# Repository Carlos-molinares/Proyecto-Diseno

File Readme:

Proyecto Diseño 
Carlos Andrés Molinares Rojas - 2210435
Jose Luis Parra Villamizar - 2210399

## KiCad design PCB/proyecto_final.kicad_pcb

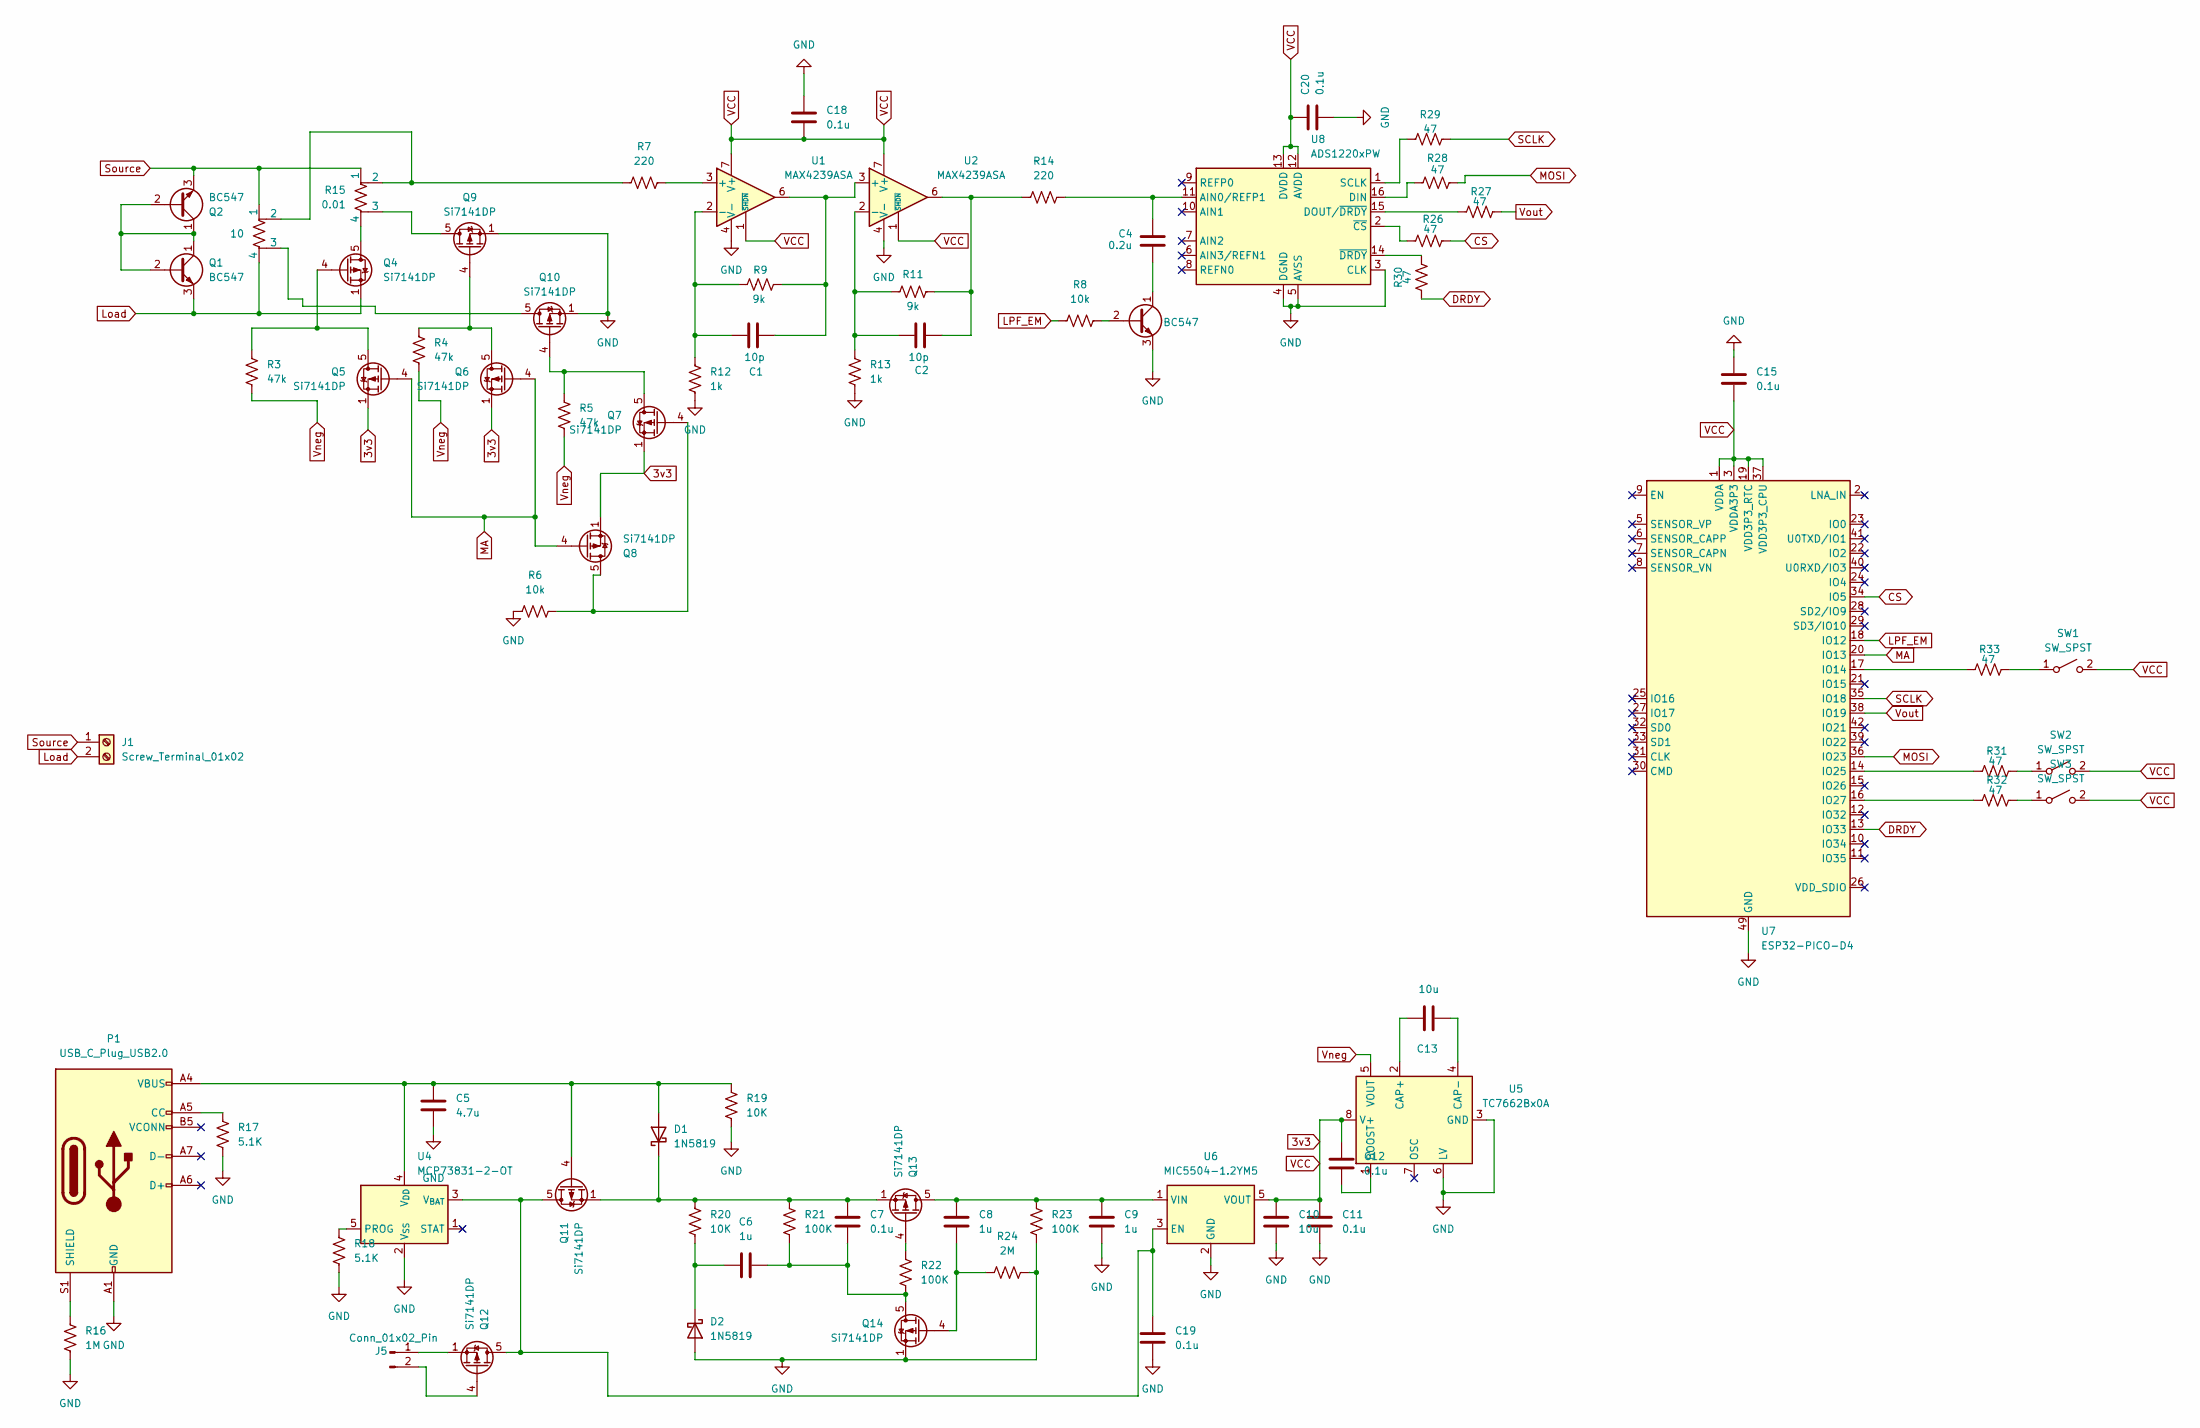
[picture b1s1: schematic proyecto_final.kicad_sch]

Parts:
C1, C2: 10p; C_0201_0603Metric
C4: 0.2u; C_0201_0603Metric
C5: 4.7u; C_0201_0603Metric
C6, C8, C9: 1u; C_0201_0603Metric
C7, C11, C12, C15, C18, C19, C20: 0.1u; C_0201_0603Metric
C10, C13: 10u; C_0201_0603Metric
D1, D2: 1N5819; D_DO-41_SOD81_P10.16mm_Horizontal
J1: Screw_Terminal_01x02; TerminalBlock_Altech_AK300-2_P5.00mm
J5: Conn_01x02_Pin; JST_EH_B2B-EH-A_1x02_P2.50mm_Vertical
P1: USB_C_Plug_USB2.0; USB_C_Plug_ShenzhenJingTuoJin_918-118A2021Y40002_Vertical
Q1, Q2, Q3: BC547; TO-92_Inline
Q4, Q5, Q6, Q7, Q8, Q9, Q10, Q11, Q12, Q13, Q14: Si7141DP; PowerPAK_SO-8_Single
R3, R4, R5: 47k; R_0201_0603Metric
R6, R8: 10k; R_0201_0603Metric
R7, R14: 220; R_0201_0603Metric
R9, R11: 9k; R_0201_0603Metric
R10: 10; R_Shunt_Ohmite_LVK12
R12, R13: 1k; R_0201_0603Metric
R15: 0.01; R_Shunt_Ohmite_LVK12
R16: 1M; R_0201_0603Metric
R17, R18: 5.1K; R_0201_0603Metric
R19, R20: 10K; R_0201_0603Metric
R21, R22, R23: 100K; R_0201_0603Metric
R24: 2M; R_0201_0603Metric
R26, R27, R28, R29, R30, R31, R32, R33: 47; R_0201_0603Metric
SW1, SW2, SW3: SW_SPST; SW_DIP_SPSTx01_Slide_6.7x4.1mm_W7.62mm_P2.54mm_LowProfile
U1, U2: MAX4239ASA; SOIC-8_3.9x4.9mm_P1.27mm
U4: MCP73831-2-OT; SOT-23-5
U5: TC7662Bx0A; SOIC-8_3.9x4.9mm_P1.27mm
U6: MIC5504-1.2YM5; SOT-23-5
U7: ESP32-PICO-D4; QFN-48-1EP_7x7mm_P0.5mm_EP5.3x5.3mm
U8: ADS1220xPW; TSSOP-16_4.4x5mm_P0.65mm

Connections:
3v3: C10.1, C11.1, C12.1, C15.2, C18.2, C20.2, Q5.1 (S), Q5.2 (S), Q5.3 (S), Q6.1 (S), Q6.2 (S), Q6.3 (S), Q7.1 (S), Q7.2 (S), Q7.3 (S), Q8.1 (S), Q8.2 (S), Q8.3 (S), SW1.2 (B), SW2.2 (B), SW3.2 (B), U1.1 (~SHDN), U1.7 (V+), U2.1 (~SHDN), U2.7 (V+), U5.8 (V+), U6.5 (VOUT), U7.1 (VDDA), U7.3 (VDDA3P3), U7.4 (VDDA3P3), U7.19 (VDD3P3_RTC), U7.37 (VDD3P3_CPU), U7.43 (VDDA), U7.46 (VDDA), U8.12 (AVDD), U8.13 (DVDD)
CS: R26.1, U7.34 (IO5)
DRDY: R30.2, U7.13 (IO33)
GND: C5.1, C9.2, C10.2, C11.2, C15.1, C18.1, C19.2, C20.1, D2.2 (A), P1.A1 (GND), P1.A12 (GND), P1.B1 (GND), P1.B12 (GND), Q3.3 (E), Q9.1 (S), Q9.2 (S), Q9.3 (S), Q10.1 (S), Q10.2 (S), Q10.3 (S), Q14.1 (S), Q14.2 (S), Q14.3 (S), R6.2, R12.2, R13.2, R16.2, R17.2, R18.2, R19.2, R23.2, R24.2, U1.4 (V-), U2.4 (V-), U4.2 (V_{SS}), U5.3 (GND), U5.6 (LV), U6.2 (GND), U7.49 (GND), U8.3 (CLK), U8.4 (DGND), U8.5 (AVSS)
LPF_EM: R8.2, U7.18 (IO12)
Load: J1.2, Q1.3 (E), Q4.1 (S), Q4.2 (S), Q4.3 (S), R10.4
MA: Q5.4 (G), Q6.4 (G), Q8.4 (G), U7.20 (IO13)
MOSI: R28.1, U7.36 (IO23)
unnamed: C2.2, R11.1, R14.2, U2.6
unnamed: C5.2, D1.2 (A), P1.A4 (VBUS), P1.A9 (VBUS), P1.B4 (VBUS), P1.B9 (VBUS), Q11.4 (G), R19.1, U4.4 (V_{DD})
unnamed: C7.2, D1.1 (K), Q11.1 (S), Q11.2 (S), Q11.3 (S), Q13.1 (S), Q13.2 (S), Q13.3 (S), R20.1, R21.1
unnamed: C6.2, D2.1 (K), R20.2
unnamed: J5.1, Q12.1 (S), Q12.2 (S), Q12.3 (S)
unnamed: J5.2, Q12.4 (G)
unnamed: P1.A5 (CC), R17.1
unnamed: P1.S1 (SHIELD), R16.1
unnamed: Q1.1 (C), Q1.2 (B), Q2.1 (C), Q2.2 (B)
unnamed: Q3.2 (B), R8.1
unnamed: C4.1, Q3.1 (C)
unnamed: Q4.5 (D), R15.4
unnamed: Q4.4 (G), Q5.5 (D), R3.1
unnamed: Q6.5 (D), Q9.4 (G), R4.1
unnamed: Q7.4 (G), Q8.5 (D), R6.1
unnamed: Q9.5 (D), R15.3
unnamed: Q10.5 (D), R10.3
unnamed: Q7.5 (D), Q10.4 (G), R5.1
unnamed: C19.1, Q11.5 (D), Q12.5 (D), U4.3 (V_{BAT}), U6.3 (EN)
unnamed: C8.1, C9.1, Q13.5 (D), R23.1, U6.1 (VIN)
unnamed: Q13.4 (G), R22.1
unnamed: C6.1, C7.1, Q14.5 (D), R21.2, R22.2
unnamed: C8.2, Q14.4 (G), R24.1
unnamed: R7.2, R10.2, R15.2
unnamed: R33.1, SW1.1 (A)
unnamed: R31.1, SW2.1 (A)
unnamed: R32.1, SW3.1 (A)
unnamed: R7.1, U1.3 (+)
unnamed: C1.1, R9.2, R12.1, U1.2 (-)
unnamed: C1.2, R9.1, U1.6, U2.3 (+)
unnamed: C2.1, R11.2, R13.1, U2.2 (-)
unnamed: R18.1, U4.5 (PROG)
unnamed: C12.2, U5.1 (BOOST)
unnamed: C13.1, U5.2 (CAP+)
unnamed: C13.2, U5.4 (CAP-)
unnamed: R33.2, U7.17 (IO14)
unnamed: R31.2, U7.14 (IO25)
unnamed: R32.2, U7.16 (IO27)
unnamed: C4.2, R14.1, U8.11 (AIN0/REFP1)
unnamed: R28.2, U8.16 (DIN)
unnamed: R27.2, U8.15 (DOUT/~DRDY)
unnamed: R29.2, U8.1 (SCLK)
unnamed: R26.2, U8.2 (~CS)
unnamed: R30.1, U8.14 (~DRDY)
SCLK: R29.1, U7.35 (IO18)
Source: J1.1, Q2.3 (E), R10.1, R15.1
Vneg: R3.2, R4.2, R5.2, U5.5 (VOUT)
Vout: R27.1, U7.38 (IO19)

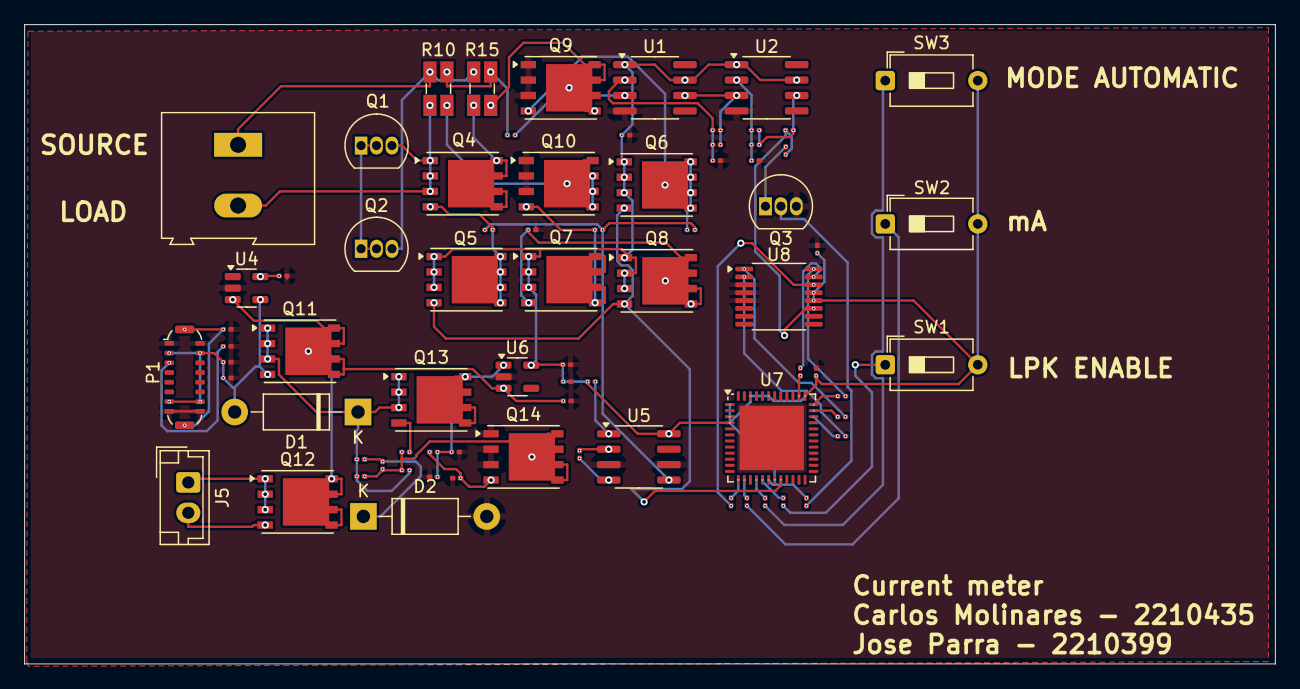
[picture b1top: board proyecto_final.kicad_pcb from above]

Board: 2 copper layers, 103.0 x 52.7 mm, 75 parts (0 on the bottom side), 56 nets.

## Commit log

2025-04-25 Create Readme
    Si
2025-04-25 Create test
2025-04-26 Create Ej
2025-04-28 Create Codigo_corrientes
2025-04-28 Codigo_corrientes
2025-04-28 Create A
2025-05-26 Create Datasheets
2025-05-26 Create Bateria
2025-05-26 Create Li-Po 3.7V 1000mAh
2025-05-26 Create nada
2025-05-27 Create pene
